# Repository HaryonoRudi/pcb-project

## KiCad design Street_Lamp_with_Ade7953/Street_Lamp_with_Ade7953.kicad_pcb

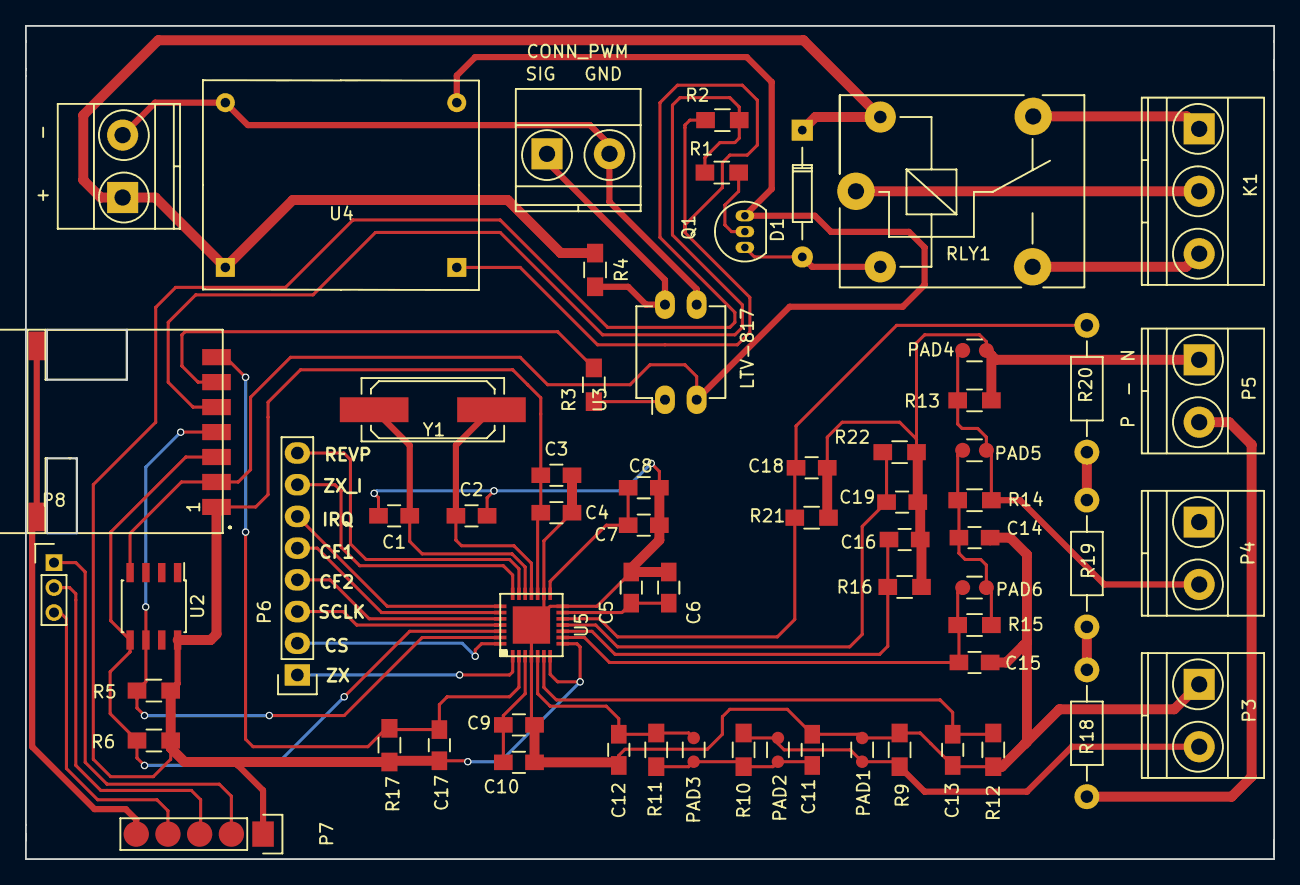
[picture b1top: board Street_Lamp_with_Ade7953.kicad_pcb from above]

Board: 2 copper layers, 100.0 x 66.8 mm, 63 parts (0 on the bottom side), 47 nets.

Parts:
+     -: INPUT_12V; TerminalBlock_Pheonix_MKDS1.5-2pol
C1, C2: 20pF; C_0805_HandSoldering
C3, C6, C8, C10: 0.1uF; C_0805_HandSoldering
C4: 10uF; C_0805_HandSoldering
C5, C7, C9: 4.7uF; C_0805_HandSoldering
C11, C12, C13, C14, C15, C16: 22nF; C_0805_HandSoldering
C17: 1uF; C_0805_HandSoldering
C18, C19: 33nF; C_0805_HandSoldering
D1: IN4148; Diode_DO-35_SOD27_Horizontal_RM10
K1: NO - C - NC; TerminalBlock_Pheonix_MKDS1.5-3pol
P3: IAP - IAN; TerminalBlock_Pheonix_MKDS1.5-2pol
P4: IBP - IBN; TerminalBlock_Pheonix_MKDS1.5-2pol
P5: P - N; TerminalBlock_Pheonix_MKDS1.5-2pol
P6: CONN_01X08; Pin_Header_Straight_1x08
P7: program_pin; Pin_Header_Straight_1x05
P8: program; Pin_Header_Straight_1x03_Pitch2.00mm
PAD1, PAD2, PAD3, PAD4, PAD5, PAD6: R_0805
Q1: BC547; TO-92_Inline_Narrow_Oval
R1, R4, R5, R6, R17: 10K; R_0805_HandSoldering
R2: 4.7K; R_0805_HandSoldering
R3, R10, R14: 100; R_0805_HandSoldering
R9, R13: R; R_0805_HandSoldering
R11, R12, R15, R16, R21, R22: 1K; R_0805_HandSoldering
R18, R19, R20: 330K; Resistor_Horizontal_RM10mm
RLY1: RELAY_12V; Relay_SANYOU_SRD_Series_Form_C
SIG   GND: CONN_PWM; TerminalBlock_Pheonix_MKDS1.5-2pol
U1: ATSAMR21B18-MZ210PA; ATSAMR21B18A-MZ210PA
U2: ECC508; SOIC-8_3.9x4.9mm_Pitch1.27mm
U3: LTV-817; DIP-4_W7.62mm_LongPads
U4: D-Sun_Regulator
U5: ADE7953
Y1: 3.68MHz; Q_49U3HMS

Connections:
3V3: C3.1, C4.1, C17.2, P7.1, R2.2, R5.2, R6.2, R17.2, U1.1, U2.8, U4.4, U5.7, U5.8, U5.17
12V: + -.1, D1.1, R4.1, RLY1.5, U4.2
AGND: C1.2, C2.2, C3.2, C4.2, C5.1, C6.1, C7.1, C8.1, C9.1, C10.1, C11.2, C12.2, C13.2, C14.2, C15.2, C16.2, C18.2, C19.2, P3.1, P4.1, P5.1, PAD1.2, PAD4.2, R9.2, R12.2, R13.2, R16.2, R21.2, R22.2, U5.4, U5.14, U5.16, U5.29
CF1: P6.5, U5.23
CF2: P6.4, U5.24
CLKIN: C2.1, U5.18, Y1.1
CLKOUT: C1.1, U5.19, Y1.2
CS: P6.2, U5.28
GND: P7.5, U1.8, U1.9
GND_SAMR: Q1.3, U1.2, U2.4, U3.2, U4.3
IAN: C13.1, R12.1, U5.6
IAP: C12.1, PAD3.1, R11.1, U5.5
IBN: C16.1, R16.1, U5.10
IBP: C15.1, PAD6.1, R15.1, U5.9
IRQ: P6.6, U5.22
MISO/SDA/Tx: R6.1, U1.3, U2.5, U5.26
MOSI/SCL/Rx: R5.1, U1.4, U2.6, U5.27
unnamed: C11.1, PAD2.1, PAD3.2, R10.2, R11.2
unnamed: C14.1, PAD5.1, PAD6.2, R14.2, R15.2
unnamed: D1.2, Q1.1, RLY1.2
unnamed: K1.1, RLY1.4
unnamed: K1.2, RLY1.1
unnamed: K1.3, RLY1.3
unnamed: P3.2, PAD1.1, PAD2.2, R9.1, R10.1
unnamed: P4.2, PAD4.1, PAD5.2, R13.1, R14.1
unnamed: P5.2, R18.1
unnamed: Q1.2, R1.1
unnamed: R3.1, U3.1
unnamed: R18.2, R19.1
unnamed: R19.2, R20.1
PA18_RELAY: R1.2, R2.1, U1.5
PA19_PWM: R3.2, U1.6
PA30: P7.3, P8.2
PA31: P7.2, P8.1
PWM_GND: + -.2, SIG GND.2, U3.3, U4.1
PWM_SIG: R4.2, SIG GND.1, U3.4
REF: C5.2, C6.2, U5.13
RESET: C17.1, R17.1, U1.7, U5.2
REVP: P6.8, U5.20
RST: P7.4, P8.3
SCLK: P6.3, U5.25
VINTA: C7.2, C8.2, U5.15
VINTD: C9.2, C10.2, U5.3
VN: C19.1, R22.1, U5.11
VP: C18.1, R20.2, R21.1, U5.12
ZX: P6.1, U5.1
ZX_I: P6.7, U5.21

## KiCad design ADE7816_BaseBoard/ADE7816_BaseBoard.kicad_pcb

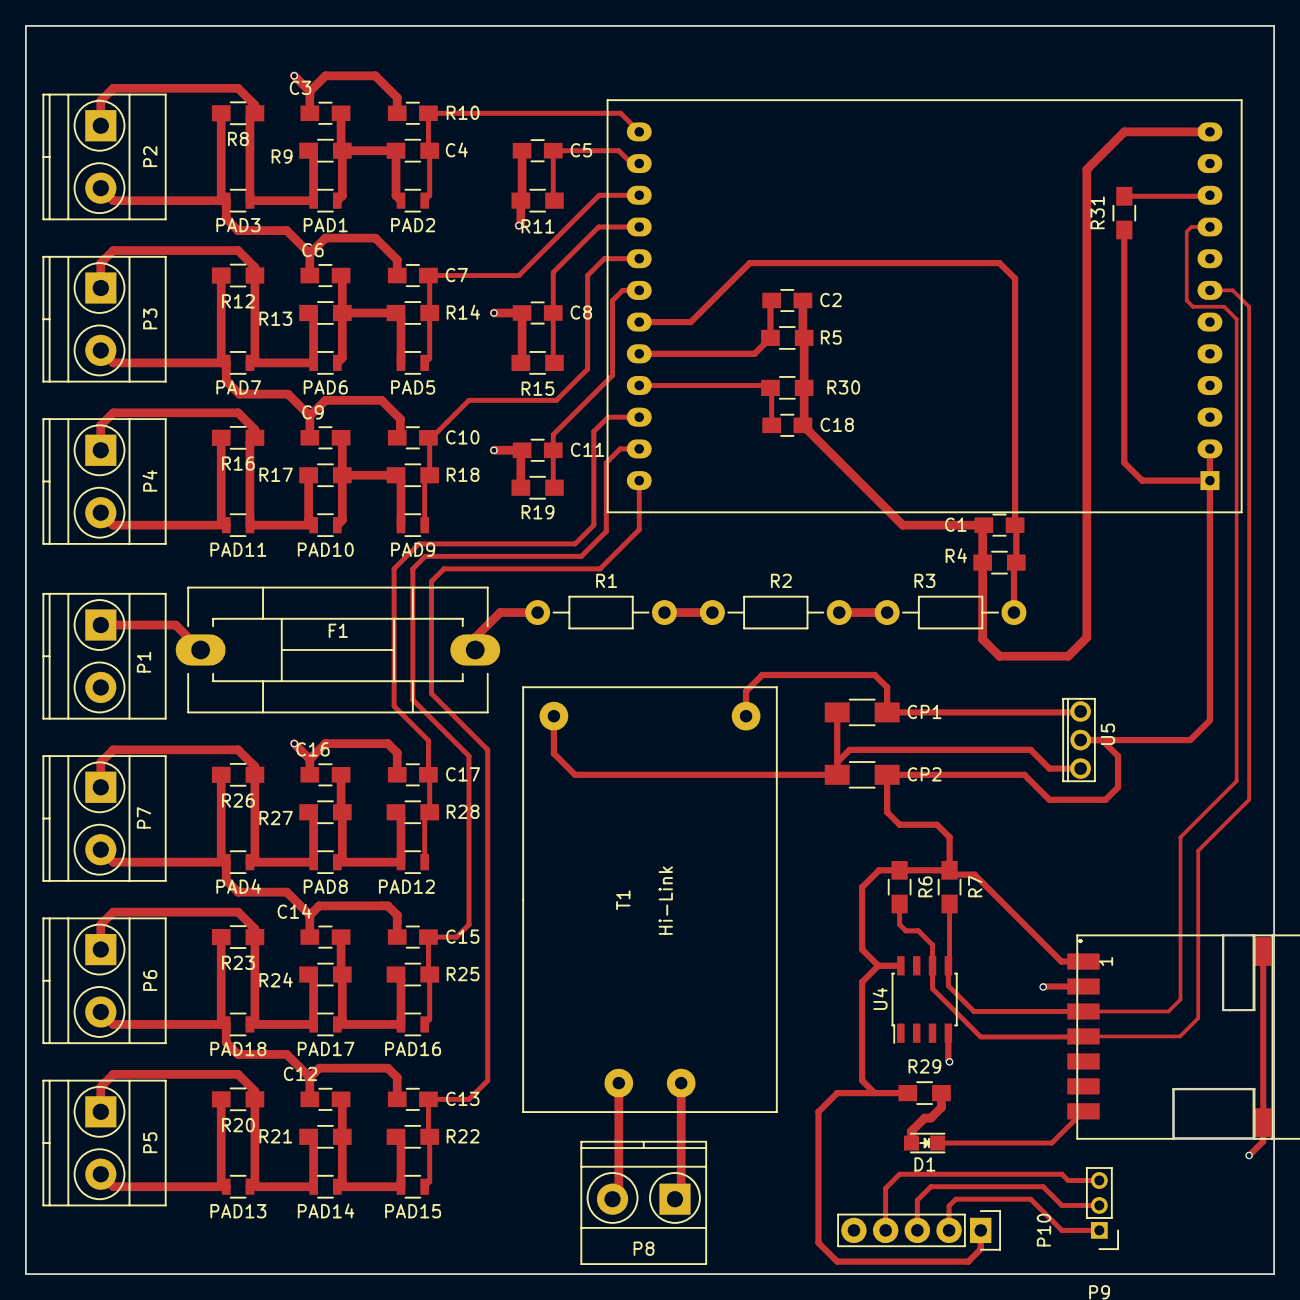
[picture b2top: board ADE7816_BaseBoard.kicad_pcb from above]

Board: 2 copper layers, 100.0 x 100.0 mm, 86 parts (0 on the bottom side), 42 nets.

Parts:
C1, C2: 33nF; C_0805_HandSoldering
C3, C4, C5, C6, C7, C8, C9, C10, C11, C12, C13, C14, C15, C16, C17, C18: 22nF; C_0805_HandSoldering
CP1: 10uF; C_1206_HandSoldering
CP2: 1uF; C_1206_HandSoldering
D1: Led; LED_0805
F1: FUSE; Fuseholder5x20_horiz_SemiClosed_Casing10x25mm
P1, P2, P3, P4, P5, P6, P7, P8: CONN_2_V; TerminalBlock_Pheonix_MKDS1.5-2pol
P9: CONN_01X03; Pin_Header_Straight_1x03_Pitch2.00mm
P10: CONN_01X05; Pin_Header_Straight_1x05
PAD1, PAD2, PAD3, PAD4, PAD5, PAD6, PAD7, PAD8, PAD9, PAD10, PAD11, PAD12, PAD13, PAD14, PAD15, PAD16, PAD17, PAD18: R_0805
R1, R2, R3: 333K; Resistor_Horizontal_RM10mm
R4, R10, R11, R15, R18, R19, R22, R25, R28, R29, R30: 1K; R_0805_HandSoldering
R5, R6, R7, R31: 10K; R_0805_HandSoldering
R8, R12, R14, R16, R20, R23, R26: R; R_0805_HandSoldering
R9, R13, R17, R21, R24, R27: 100; R_0805_HandSoldering
T1: Hi-Link
U1: ADE7816-Breakout; ade7816-breakout
U3: ATSAMR21B18-MZ210PA; ATSAMR21B18A-MZ210PA
U4: ECC508; SOIC-8_3.9x4.9mm_Pitch1.27mm
U5: LD1117; TO-251AA

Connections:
+3V3: CP2.1, P10.1, R6.1, R7.1, R29.1, R31.1, U1.1, U1.2, U3.1, U4.8, U5.2
GNDA: C1.2, C2.2, C3.2, C4.2, C5.2, C6.2, C7.2, C8.2, C9.2, C10.2, C11.2, C12.2, C13.2, C14.2, C15.2, C16.2, C17.2, C18.2, P1.2, P2.2, P3.2, P4.2, P5.2, P6.2, P7.2, PAD3.1, PAD4.1, PAD7.1, PAD11.1, PAD13.1, PAD18.1, R4.2, R5.2, R8.2, R11.2, R12.2, R15.2, R16.2, R19.2, R20.2, R23.2, R26.2, R30.2, U1.3, U1.12
GNDD: CP1.2, CP2.2, P10.5, T1.4, U3.2, U3.8, U3.9, U4.4, U5.1
IAN: C5.1, R11.1, U1.23
IAP: C4.1, PAD2.2, R10.2, U1.24
IBN: C8.1, R15.1, U1.21
IBP: C7.1, PAD5.2, R14.2, U1.22
ICN: C11.1, R19.1, U1.19
ICP: C10.1, PAD9.2, R18.2, U1.20
IDP: C13.1, PAD15.2, R22.2, U1.13
IEP: C15.1, PAD16.2, R25.2, U1.14
IFP: C17.1, PAD12.2, R28.2, U1.15
IN: C18.1, R30.1, U1.16
MOSI/SDA: R7.2, U1.9, U3.3, U4.5
unnamed: C3.1, PAD1.2, PAD2.1, R9.2, R10.1
unnamed: C6.1, PAD5.1, PAD6.2, R13.2, R14.1
unnamed: C9.1, PAD9.1, PAD10.2, R17.2, R18.1
unnamed: C12.1, PAD14.2, PAD15.1, R21.2, R22.1
unnamed: C14.1, PAD16.1, PAD17.2, R24.2, R25.1
unnamed: C16.1, PAD8.2, PAD12.1, R27.2, R28.1
unnamed: CP1.1, T1.3, U5.3
unnamed: D1.2, R29.2
unnamed: F1.1, P1.1
unnamed: F1.2, R1.1
unnamed: P2.1, PAD1.1, PAD3.2, R8.1, R9.1
unnamed: P3.1, PAD6.1, PAD7.2, R12.1, R13.1
unnamed: P4.1, PAD10.1, PAD11.2, R16.1, R17.1
unnamed: P5.1, PAD13.2, PAD14.1, R20.1, R21.1
unnamed: P6.1, PAD17.1, PAD18.2, R23.1, R24.1
unnamed: P7.1, PAD4.2, PAD8.1, R26.1, R27.1
unnamed: P8.1, T1.1
unnamed: P8.2, T1.2
unnamed: R1.2, R2.1
unnamed: R2.2, R3.1
PA07: D1.1, U3.7
PA17/SCL: R6.2, U1.7, U3.4, U4.6
PA30: P9.2, P10.3
PA31: P9.1, P10.2
RST: P9.3, P10.4
SS/HSA: R31.2, U1.10
VN: C2.1, R5.1, U1.17
VP: C1.1, R3.2, R4.1, U1.18

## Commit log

2016-08-09 schematic pcb
